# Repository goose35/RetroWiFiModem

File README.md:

# Retro WiFi modem

Forked from BenMtl's repository.
Modified to use a NodeMCU board, of which i had several in waiting.
Will be using on a C64, BBC Micro and Amiga A1200 so will require several adapter leads

# Important Note

Please note that there are 2 standards (pin-outs) for the 10 pin motherboard connector
AT/Everex or Intel/DTK
This modem is using the Intel/DTK pinout
Therefore be aware of this when buying/making your connections to the modem serial port

## The Software

In a nod to its popularity, the command set I used largely follows that
used in [Paul Rickards' WiFi232](http://biosrhythm.com/?page_id=1453)
modem. Even if the innards are completely different, it made sense to
make it *work* like what people were already used to. There's a reason
everyone's been copying the Hayes command set for almost 40 years!

### First time setup

The default serial configuration is 1200bps, 8 data bits, no parity, 1
stop bit.

Here's the commands you need to set up the modem to automatically
connect to your WiFi network:

1. `AT$SSID=your WiFi network name` to set the WiFi network that the
modem will connect to when it powers up.
2. `AT$PASS=your WiFi network password` to set the password for the
network.
3. `ATC1` to connect to the network.
4. Optional stuff:
   * `AT$SB=speed` to set the default serial speed.
   * `AT$SU=dps` to set the data bits, parity and stop bits.
   * `ATNETn` to select whether or not to use Telnet protocol.
   * `AT&Kn` to use RTS/CTS flow control or not.
5. `AT&W` to save the settings.

Once you've done that, the modem will automatically connect to your WiFi
network on power up and will be ready to "dial up" a connection with
ATDT.

### Command Reference

Multiple AT commands can be typed in on a single line. Spaces between
commands are allowed, but not within commands (i.e. AT S0=1 X1 Q0 is
fine; ATS 0=  1 is not). Commands that take a string as an argument
(e.g. AT$SSID=, AT$TTY=) assume that *everything* that follows is a part
of the string, so no commands are allowed after them.

Command | Details
------- | -------
+++     | Online escape code. Once your modem is connected to another device, the only command it recognises is an escape code of a one second pause followed by three typed plus signs and another one second pause, which puts the modem back into local command mode.
A/      | Repeats the last command entered. Do not type AT or press Enter.
AT      | The attention prefix that precedes all command except A/ and +++.
AT?     | Displays a help cheatsheet.
ATA     | Force the modem to answer an incoming connection when the conditions for auto answer have not been satisfied.
ATC?<br>ATC*n* | Query or change the current WiFi connection status. A result of 0 means that the modem is not connected to WiFi, 1 means the modem is connected. The command ATC0 disconnects the modem from a WiFi connection. ATC1 connects the modem to the WiFi.
ATDS*n* | Calls the host specified in speed dial slot *n* (0-9).
ATDT<i>[+=-]host[:port]</i> | Tries to establish a WiFi TCP connection to the specified host name or IP address. If no port number is given, 23 (Telnet) is assumed. You can also use ATDT to dial one of the speed dial slots in one of two ways:<br><br><ul><li>The alias in each speed dial slot is checked to see if it matches the specified hostname.</li><li>A host specified as 7 identical digits dials the slot indicated by the digit. (i.e. 2222222 would speed dial the host in slot 2).</li></ul>Preceding the host name or IP address with a +, = or - character overrides the ATNET setting for the period of the connection.<br><br><ul><li>**+** forces NET2 (fake Telnet)</li><li>**=** forces NET1 (real Telnet)</li><li>**-** forces NET0 (no Telnet)</li></ul>Once the dial attempt has begun, pressing any key before the connection is established will abort the attempt.
ATE?<br>ATE*n* | Command mode echo. Enables or disables the display of your typed commands.<br><br><ul><li>E0 Command mode echo OFF. Your typing will not appear on the screen.</li><li>E1 Command mode echo ON. Your typing will appear on the screen.</li></ul>
ATGET*http&#58;//host[/page]* | Displays the contents of a website page. **https** connections are not supported. Once the contents have been displayed, the connection will automatically terminate.
ATH | Hangs up (ends) the current connection.
ATI | Displays the current network status, including sketch build date, WiFi and call connection state, SSID name, IP address, and bytes transferred.
ATNET?<br>ATNET*n* | Query or change whether telnet protocol is enabled. A result of 0 means that telnet protocol is disabled; 1 is *Real* telnet protocol and 2 is *Fake* telnet protocol. If you are connecting to a telnet server, it may expect the modem to respond to various telnet commands, such as terminal name (set with `AT$TTY`), terminal window size (set with `AT$TTS`) or terminal speed. Telnet protocol should be enabled for these sites, or you will at best see occasional garbage characters on your screen, or at worst the connection may fail.<br><br>The difference between *real* and *fake* telnet protocol is this: with *real* telnet protocol, a carriage return (CR) character being sent from the modem to the telnet server always has a NUL character added after it. The implementation of the telnet protocol used by some BBSes doesn't properly strip out the NUL character. When connecting to such BBSes (Particles! is one), use *fake* telnet.<br><br>When using *real* telnet protocol, when the telnet server sends a CR character followed by a NUL character, only the CR character will be sent to the serial port; the NUL character will be silently stripped out. With *fake* telnet protocol, the NUL will be passed through.
ATO | Return online. Use with the escape code (+++) to toggle between command and online modes.
ATQ?<br>ATQ*n* | Enable or disable the display of result codes. The default is Q0.<br><br><ul><li>Q0 Display result codes.</li><li>Q1 Suppress result codes (quiet).</li></ul>
ATRD<br>ATRT | Displays the current UTC date and time from NIST in the format *YY-MM-DD HH:MM:SS*. A WiFi connection is required and you cannot be connected to another site.
ATS0?<br>ATS0=*n* | Display or set the number of "rings" before answering an incoming connection. Setting `S0=0` means "don't answer".
ATV?<br>ATV*n* | Display result codes in words or numbers. The default is V1.<br><br><ul><li>V0 Display result codes in numeric form.</li><li>V1 Display result codes in text form.</li></ul>
ATX?<br>ATX*n* | Control the amount of information displayed in the result codes. The default is X1 (extended codes).<br><br><ul><li>X0 Display basic codes (CONNECT, NO CARRIER)</li><li>X1 Display extended codes (CONNECT speed, NO CARRIER (connect time))</li></ul>
ATZ | Resets the modem.
AT&F | Reset the NVRAM contents and current settings to the sketch defaults. All settings, including SSID name, password and speed dial slots are affected.
AT&K?<br>AT&K*n* | Data flow control. Prevents the modem's buffers for received and transmitted from overflowing.<br><br><ul><li>&K0 Disable data flow control.</li><li>&K1 Use hardware flow control. Requires that your computer and software support Clear to Send (CTS) and Request to Send (RTS) at the RS-232 interface.</li></ul>
AT&R?<br>AT&R=*server pwd* | Query or change the password for incoming connections. If set, the user has 3 chances in 60 seconds to enter the correct password or the modem will end the connection.
AT&V*n* | Display current or stored settings.<br><br><ul><li>&V0 Display current settings.</li><li>&V1 Display stored settings.</li></ul>
AT&W | Save current settings to NVRAM.
AT&Zn?<br>AT&Z*n*=*host[:port],alias* | Store up to 10 numbers in NVRAM, where *n* is the position 0-9 in NVRAM, and *host[:port]* is the host string, and *alias* is the speed dial alias name. The host string may be up to 50 characters long, and the alias string may be up to 16 characters long.<br><br>Example: `AT&Z2=particlesbbs.dyndns.org:6400,particles`<br><br>This number can then be dialed in any of the following ways:<br><br><ul><li>`ATDS2`</li><li>`ATDTparticles`</li><li>`ATDT2222222`</li></ul>
AT$AE?<br>AT$AE=*startup AT cmd* | Query or change the command line to be executed when the modem starts up.
AT$BM?<br>AT$BM=*server busy msg* | Query or change a message to be returned to an incoming connection if the modem is busy (i.e. already has a connection established).
AT$MDNS<br>AT$MDNS=*mDNS name* | Query or change the mDNS network name (defaults to "espmodem"). When a non zero TCP port is defined, you can telnet to that port with **telnet mdnsname.local port**.
AT$PASS?<br>AT$PASS=*WiFi pwd* | Query or change the current WiFi password. The password is case sensitive. Clear the password by issuing the set command with no password. The maximum length of the password is 64 characters.
AT$SB?<br>AT$SB=*n* | Query or change the current baud rate. Valid values for "n" are 110, 300, 450, 600, 710, 1200, 2400, 4800, 9600, 19200, 38400, 57600, 76800 and 115200. Any other value will return an ERROR message. The default baud rate is 1200. The Retro WiFi modem does not automatically detect baud rate like a dial-up modem. The baud rate setting must match that of your terminal to operate properly. It will display garbage in your terminal otherwise.
AT$SP?<br>AT$SP=*n* | TCP server port to listen on. A value of 0 means that the TCP server is disabled, and no incoming connections are allowed.
AT$SSID?<br>AT$SSID=*ssid name* | Query or change the current SSID to the specified name. The given SSID name is case sensitive. Clear the SSID by issuing the set command with no SSID. The maximum length of the SSID name is 32 characters.
AT$SU?<br>AT$SU=*dps* | Query or change the current number of data bits ('d'), parity ('p') and stop bits ('s") of the serial UART. Valid values for 'd' are 5, 6, 7 or 8 bits. Valid values for 'p' are (N)one, (O)dd or (E)ven parity. Valid values for 's' are 1 or 2 bits. The default settings are 8N1. The UART setting must match your terminal to work properly.
AT$TTL?<br>AT$TTL=*telnet location* | Query or change the Telnet location value to be returned when the Telnet server issues a SEND-LOCATION request. The default value is "Computer Room".
AT$TTS?<br>AT$TTS=*WxH* | Query or change the window size (columns x rows) to be returned when the Telnet server issues a NAWS (Negotiate About Window Size) request. The default value is 80x24. For terminals that are smaller than 80x24, setting these values appropriately will enable paging on the help (AT?) and network status (ATI) commands.
AT$TTY?<br>AT$TTY=*terminal type* | Query or change the terminal type to be returned when the Telnet server issues a TERMINAL-TYPE request. The default value is "ansi".
AT$W?<br>AT$W=*n* | Startup wait.<br><br><ul><li>$W=0 Startup with no wait.</li><li>$W=1 Wait for the return key to be pressed at startup.</li></ul>

### Updating the Software

While I liked the idea of being able to update the software OTA, it
seemed to make more sense in my situation to be able to *push* a new
version as I built it rather than have the modem *pull* it. So that's
what I did. It uses the default OTA upload capability built into the
Arduino IDE.

**Jan 24/22:** It's been reported that the ESP8266 core is slightly
snafu'd at the moment, and that it's breaking things in the modem
software. As a workaround, I've added the bin file that gets uploaded
to the modem in the repository. I haven't updated my ESP8266 core in
ages; "if it isn't broken, don't break it", and everything still works
for me. The bin file can be uploaded with the *espota.py* tool in the
ESP8266 tool directory tree.

(If TPTB have deleted/renamed/moved that tool in the current core,
you'll have to figure out how to do a manual OTA update.)

### RTS/CTS handshaking and a dead spin loop issue

Something I noticed with ESP8266 software that puzzled me was the
number of places I saw a series of Serial print statements being broken
up with calls to yield(), like so:

```
   Serial.print("Hello world!\n");
   yield();
   Serial.print("How are you today?\n");
   yield();
```
It didn't take long to figure out what was going on; The print() call
was blocking, and at lower baud rates, even printing a few relatively
short strings was enough to cause the watchdog to bark and cause a
reset. So the repetitive yield() calls were an attempt to feed the
watchdog often enough to keep it from barking.

What does this have to do with RTS/CTS handshaking? Simply put,
lowering RTS for more than a few seconds was causing the watchdog to
bark as well. So I started digging.

In cores/esp8266/uart.cpp I found the following function:

```
static void
uart_do_write_char(const int uart_nr, char c)
{
    while(uart_tx_fifo_full(uart_nr));

    USF(uart_nr) = c;
}
```

This is the low level function that everything calls to send a character
out the serial port. The cause of the watchdog barking is in the dead
spin while loop. It waits until there's room in the transmit FIFO to add
another character. So if RTS/CTS handshaking is enabled, and RTS is low
for longer than the watchdog likes: woof.

What I did to quiet the watchdog down both when sending long strings at
low baud rates and during long waits for RTS to come active again was to
add a yield() call to the dead spin while loop, like so:

```
static void
uart_do_write_char(const int uart_nr, char c)
{
    while(uart_tx_fifo_full(uart_nr))
      yield();

    USF(uart_nr) = c;
}
```

This way, no matter how long the code has to wait for space in the
transmit FIFO, the watchdog is kept well fed and quiet.

## Status

Is a personal project like this ever *really* finished? I've had two
units assembled and in use since the spring of 2020, and while there's
been some software changes since then, I really don't expect any more.
There are no outstanding bugs that I'm aware of, and no new features on
my wish list. For the time being at least, I think it's complete.

### Linux, Telnet, Zmodem and downloading binary files

Have you used the modem to 'dial' into a Linux box? And have you done a
`sz binary_file` on the Linux box? And at a completely reproducible
point in the file, has the connection dropped? But other binary files
work just fine? Then read on.

This drove me slightly batty for months. I finally narrowed it down to
trying to send blocks of binary data with a large number of FF bytes. I
eventually created a test file consisting of 2K of FF and used that to
test with. I could download it through the modem with Xmodem just fine.
Ymodem also worked if I kept the block size down to 128 bytes - but the
connection would drop instantly if I tried sending 1K blocks. Same thing
with Zmodem.

In fact, if I just tried `cat binary_file`, the connection would
drop. Which eventually got me thinking. Sitting at the console on my
main Linux box, I telnet'd to the same box and logged in. No WiFi modem
involved anywhere, just a telnet session on the console to the same box.
I then did a `cat binary_file`. The telnet connection dropped, and I
was back in my original session.

It's the Linux telnet daemon. Not the modem at all.

To prove it to myself, I hooked up WiFi modems to two systems on their
serial ports and had one dial into the other. I could send the all FF
binary file back and forth with Zmodem and Ymodem, no trouble at all.

But you really, really need to download that binary file through the
modem from a telnet connection to a Linux box? You're not going to be
able to use Zmodem. Ymodem will work (the sy command defaults to 128
byte blocks), as will Xmodem. But not Zmodem.

Oddly enough, the telnet daemon has no trouble *receiving* the all FF
binary file. Only sending it. Your guess as to why is probably better
than mine.

## References

* [WiFi232 - An Internet Hayes Modem for your Retro Computer](http://biosrhythm.com/?page_id=1453)<br>
* [WiFi232's Evil Clone](https://forum.vcfed.org/index.php?threads/wifi232s-evil-clone.1070412/)<br>
* [Jussi Salin's Virtual modem for ESP8266](https://github.com/jsalin/esp8266_modem)<br>
* [Stardot's ESP8266 based virtual modem](https://github.com/stardot/esp8266_modem)<br>
* [Roland Juno's ESP8266 based virtual modem](https://github.com/RolandJuno/esp8266_modem)

## Acknowledgements

* A whole lot of people owe a big vote of thanks to Jussi Salin for
releasing their virtual modem code for the ESP8266 and starting the
ball rolling.
* Paul Rickards for an amazing bit of hardware to draw inspiration from.
* All the Stardot contributors for their work.
* And, of course, Dennis C. Hayes for creating something so simple and
elegant that has stood the test of time.

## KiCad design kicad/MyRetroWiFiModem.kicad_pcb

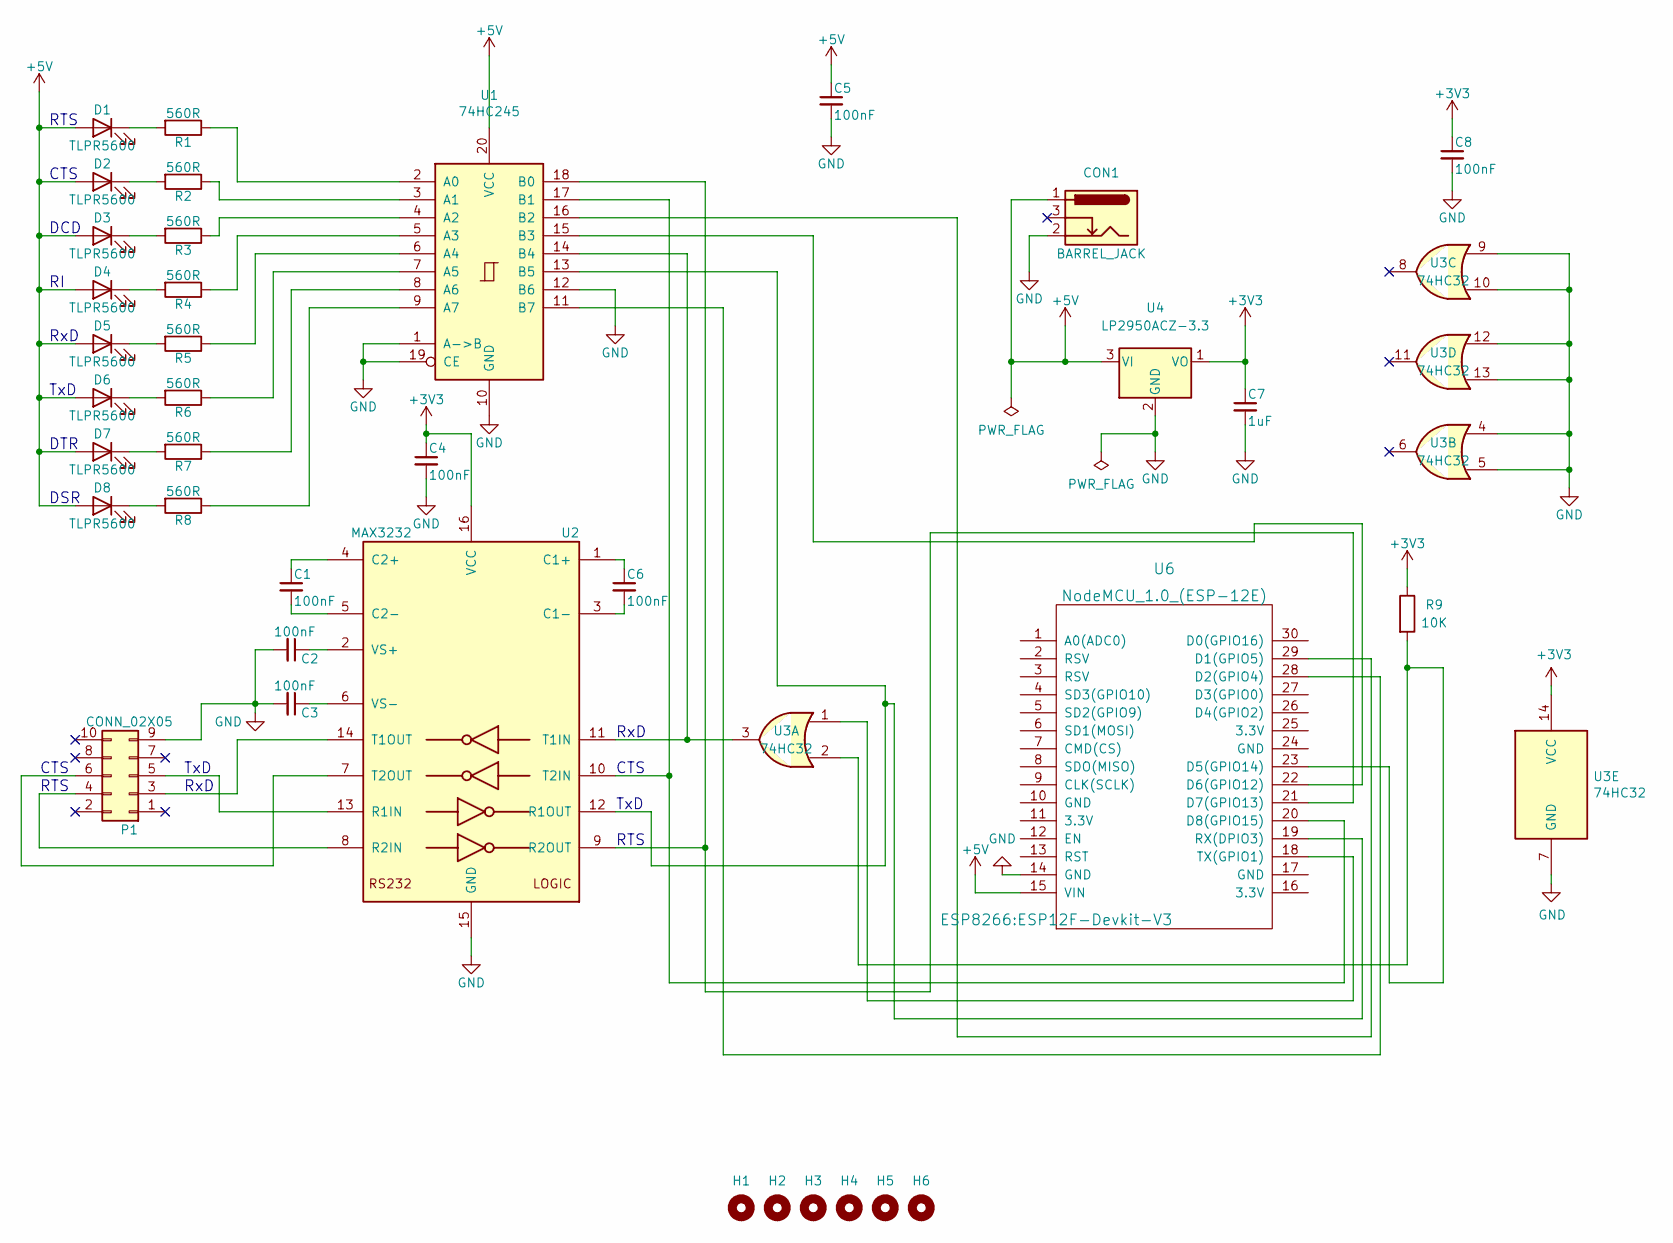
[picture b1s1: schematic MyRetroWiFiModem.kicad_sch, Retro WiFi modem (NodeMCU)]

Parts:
C1, C2, C3, C4, C5, C8: 100nF; C_Disc_D3.0mm_W2.0mm_P2.50mm; DigiKey PN 399-9859-1-ND
C6: 100nF; C_Disc_D5.0mm_W2.5mm_P2.50mm; DigiKey PN 399-9843-ND
C7: 1uF; C_Disc_D5.0mm_W2.5mm_P5.00mm; DigiKey PN 399-3529-ND
CON1: BARREL_JACK; BarrelJack_Horizontal; DigiKey PN 839-54-00166-ND
D1, D2, D3, D4, D5, D6, D7, D8: TLPR5600; LED_D3.0mm; DigiKey PN TLPR5600-ND
H1, H2, H3, H4, H5, H6: MountingHole; MountingHole_3.2mm_M3
P1: CONN_02X05; IDC-Header_2x05_P2.54mm_Vertical; DigiKey PN ED1543-ND
R1, R2, R3, R4, R5, R6, R7, R8: 560R; R_Axial_DIN0204_L3.6mm_D1.6mm_P7.62mm_Horizontal; DigiKey PN CF18JT560RCT-ND
R9: 10K; R_Axial_DIN0204_L3.6mm_D1.6mm_P7.62mm_Horizontal; DigiKey PN CF18JT10K0CT-ND
U1: 74HC245; DIP-20_W7.62mm; DigiKey PN 296-1612-5-ND
U2: MAX3232; DIP-16_W7.62mm; DigiKey PN ICL3232CPZ-ND
U3: 74HC32; DIP-14_W7.62mm; DigiKey PN 296-1589-5-ND
U4: LP2950ACZ-3.3; TO-92L_Inline_Wide; DigiKey PN LP2950ACZ-3.3GOS-ND
U6: NodeMCU_1.0_(ESP-12E); ESP12F-Devkit-V3

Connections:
+3V3: C4.1, C7.1, C8.1, R9.1, U2.16 (VCC), U3.14 (VCC), U4.1 (VO)
+5V: C5.1, CON1.1, D1.2 (A), D2.2 (A), D3.2 (A), D4.2 (A), D5.2 (A), D6.2 (A), D7.2 (A), D8.2 (A), U1.20 (VCC), U4.3 (VI), U6.15 (VIN)
GND: C2.2, C3.2, C4.2, C5.2, C7.2, C8.2, CON1.2, P1.9, U1.1 (A->B), U1.10 (GND), U1.12 (B6), U1.19 (CE), U2.15 (GND), U3.4, U3.5, U3.7 (GND), U3.9, U3.10, U3.12, U3.13, U4.2 (GND), U6.14 (GND)
unnamed: C1.1, U2.4 (C2+)
unnamed: C1.2, U2.5 (C2-)
unnamed: C2.1, U2.2 (VS+)
unnamed: C3.1, U2.6 (VS-)
unnamed: C6.1, U2.1 (C1+)
unnamed: C6.2, U2.3 (C1-)
unnamed: D1.1 (K), R1.2
unnamed: D2.1 (K), R2.2
unnamed: D3.1 (K), R3.2
unnamed: D4.1 (K), R4.2
unnamed: D5.1 (K), R5.2
unnamed: D6.1 (K), R6.2
unnamed: D7.1 (K), R7.2
unnamed: D8.1 (K), R8.2
unnamed: P1.3, U2.14 (T1OUT)
unnamed: P1.4, U2.8 (R2IN)
unnamed: P1.5, U2.13 (R1IN)
unnamed: P1.6, U2.7 (T2OUT)
unnamed: R1.1, U1.2 (A0)
unnamed: R2.1, U1.3 (A1)
unnamed: R3.1, U1.4 (A2)
unnamed: R4.1, U1.5 (A3)
unnamed: R5.1, U1.6 (A4)
unnamed: R6.1, U1.7 (A5)
unnamed: R7.1, U1.8 (A6)
unnamed: R8.1, U1.9 (A7)
unnamed: R9.2, U3.2, U6.23 (D5(GPIO14))
unnamed: U1.11 (B7), U6.28 (D2(GPIO4))
unnamed: U1.13 (B5), U2.12 (R1OUT), U6.19 (RX(DPIO3))
unnamed: U1.14 (B4), U2.11 (T1IN), U3.3
unnamed: U1.15 (B3), U6.22 (D6(GPIO12))
unnamed: U1.16 (B2), U6.29 (D1(GPIO5))
unnamed: U1.17 (B1), U2.10 (T2IN), U6.20 (D8(GPIO15))
unnamed: U1.18 (B0), U2.9 (R2OUT), U6.21 (D7(GPIO13))
unnamed: U3.1, U6.18 (TX(GPIO1))

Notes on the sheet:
TxD
CTS
RxD
RTS
DSR
DCD
DTR

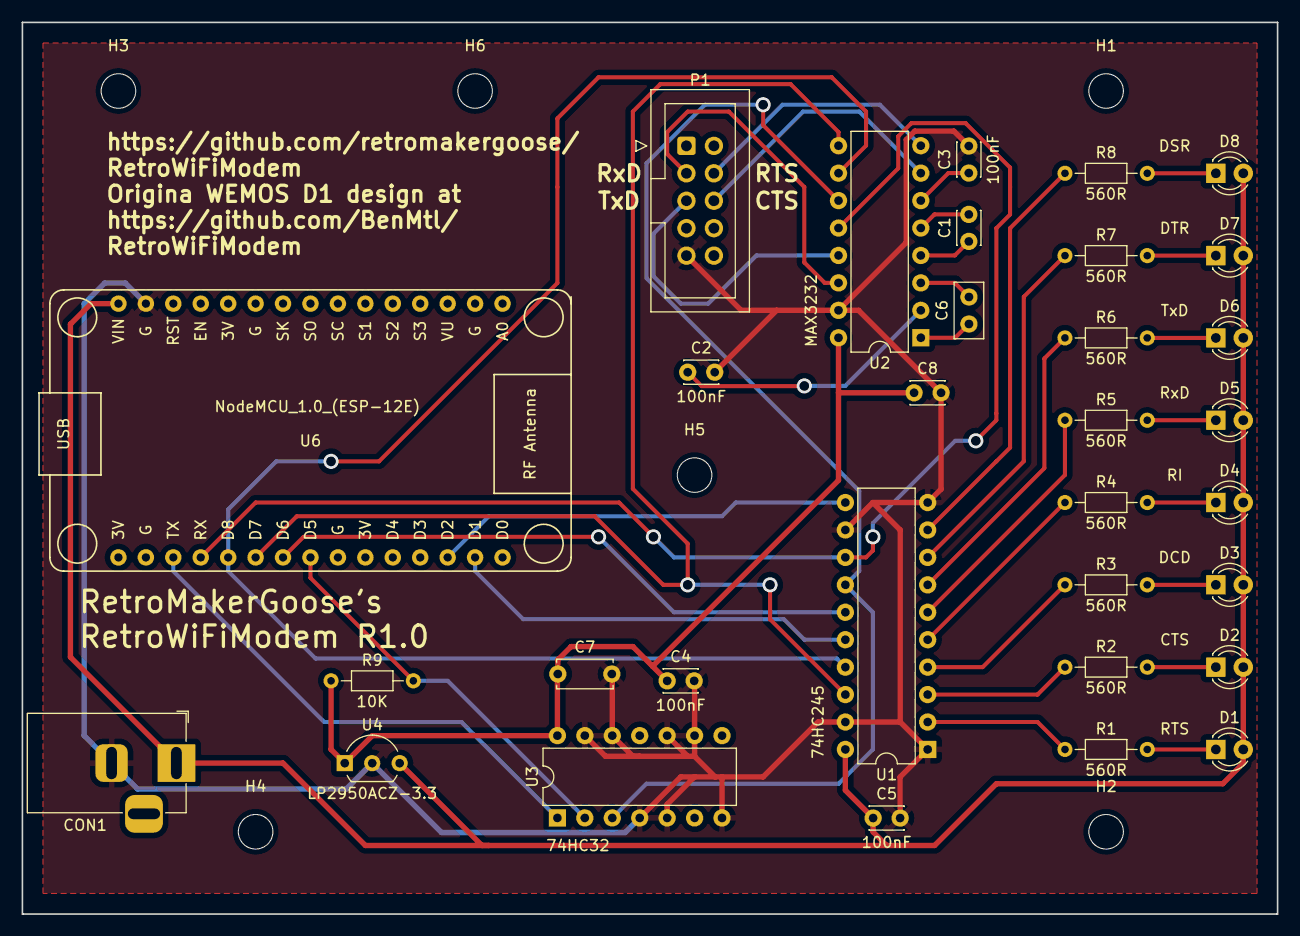
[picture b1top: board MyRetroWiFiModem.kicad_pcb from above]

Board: 2 copper layers, 116.2 x 82.5 mm, 38 parts (0 on the bottom side), 38 nets.

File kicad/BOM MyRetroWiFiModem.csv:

"Id";"Designator";"Package";"Quantity";"Designation";"Supplier and ref";
1;"U6";"NodeMCU1.0(12-E)";1;"NodeMCU_1.0_(ESP-12E)";;;
2;"C2,C3,C4,C8,C5,C1";"C_Disc_D3.0mm_W2.0mm_P2.50mm";6;"100nF";;;
3;"R9";"R_Axial_DIN0204_L3.6mm_D1.6mm_P7.62mm_Horizontal";1;"10K";;;
4;"R7,R5,R6,R4,R8,R3,R1,R2";"R_Axial_DIN0204_L3.6mm_D1.6mm_P7.62mm_Horizontal";8;"560R";;;
5;"H4,H3,H1,H6,H2,H5";"MountingHole_3.2mm_M3";6;"MountingHole";;;
6;"U1";"DIP-20_W7.62mm";1;"74HC245";;;
7;"P1";"IDC-Header_2x05_P2.54mm_Vertical";1;"CONN_02X05";;;
8;"D5,D8,D4,D2,D7,D1,D6,D3";"LED_D3.0mm";8;"TLPR5600";;;
9;"C6";"C_Disc_D5.0mm_W2.5mm_P5.00mm";1;"100nF";;;
10;"U4";"TO-92L_Inline_Wide";1;"LP2950ACZ-3.3";;;
11;"CON1";"BarrelJack_Horizontal";1;"BARREL_JACK";;;
12;"U2";"DIP-16_W7.62mm";1;"MAX3232";;;
13;"U3";"DIP-14_W7.62mm";1;"74HC32";;;
14;"C7";"C_Disc_D3.0mm_W2.0mm_P2.50mm";1;"1uF";;;

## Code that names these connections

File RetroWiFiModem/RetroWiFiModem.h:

#ifndef _MODEM_H
   #define _MODEM_H

   #define DEBUG                 0
   #define DEFAULT_SPEED         1200

   #define RING_INTERVAL         1500
   #define MAX_CMD_LEN           256
   #define TX_BUF_SIZE           256
   #define ESC_CHAR              '+'
   #define ESC_COUNT             3
   #define GUARD_TIME            1000
   #define MAGIC_NUMBER          0x4321
   #define MAX_SSID_LEN          32
   #define MAX_WIFI_PWD_LEN      64
   #define DEFAULT_LISTEN_PORT   6400
   #define TELNET_PORT           23
   #define HTTP_PORT             80
   #define SPEED_DIAL_SLOTS      10
   #define MAGIC_ANSWER_RINGS    3
   #define MAX_ALIAS_LEN         16
   #define MAX_SPEED_DIAL_LEN    50
   #define MAGIC_SPEED_LEN       7
   #define MAX_MDNSNAME_LEN      80
   #define MAX_BUSYMSG_LEN       80
   #define MAX_PWD_LEN           80
   #define PASSWORD_TIME         60000
   #define PASSWORD_TRIES        3
   #define MAX_AUTOEXEC_LEN      80
   #define MAX_TERMINAL_LEN      80
   #define MAX_LOCATION_LEN      80

   #define NUL  '\x00'
   #define CTLC '\x03'
   #define BS   '\x08'
   #define LF   '\x0A'
   #define CR   '\x0D'
   #define DEL  '\x7F'

   #define NO_TELNET   ((uint8_t)0)
   #define REAL_TELNET ((uint8_t)1)
   #define FAKE_TELNET ((uint8_t)2)

   // Telnet codes
   #define VLSUP     ((uint8_t)0)
   #define VLREQ     ((uint8_t)1)
   #define LOC       ((uint8_t)23)
   #define TTYPE     ((uint8_t)24)
   #define NAWS      ((uint8_t)31)
   #define TSPEED    ((uint8_t)32)
   #define LFLOW     ((uint8_t)33)
   #define LINEMODE  ((uint8_t)34)
   #define XDISPLOC  ((uint8_t)35)
   #define NEW_ENVIRON ((uint8_t)39)
   #define BINARY    ((uint8_t)0)
   #define ECHO      ((uint8_t)1)
   #define SUP_GA    ((uint8_t)3)
   #define SE        ((uint8_t)240)
   #define SB        ((uint8_t)250)
   #define WILL      ((uint8_t)251)
   #define WONT      ((uint8_t)252)
   #define DO        ((uint8_t)253)
   #define DONT      ((uint8_t)254)
   #define IAC       ((uint8_t)255)

   #define NIST_HOST "time.nist.gov"
   #define NIST_PORT 13

   #define ACTIVE LOW           // RS232 control signals are active low

   // As the ESP8266 is being used as a modem (DCE) in this application,
    // I've reversed the naming of RTS/CTS to match what they'd be on
    // a modem. The usual naming is correct if the ESP8266 is wired up as
    // a DTE, but kept confusing me here as it's wired up as a DCE.
   #ifdef ARDUINO_ESP8266_WEMOS_D1R1
      // D1 R1 pins
      #define CTS D10           // (GPIO15) output
      #define RTS D11           // (GPIO13) input
      #define RI  D12           // (GPIO12) output
      #define DSR D4            // (GPIO04) output
      #define DCD D3            // (GPIO05) output
      #define TXEN D5           // (GPIO14) output
   #endif

   #ifdef ARDUINO_ESP8266_WEMOS_D1MINI
      // D1 mini pins
      #define CTS D8            // (GPIO15) output
      #define RTS D7            // (GPIO13) input
      #define RI  D6            // (GPIO12) output
      #define DSR D2            // (GPIO04) output
      #define DCD D1            // (GPIO05) output
      #define TXEN D5           // (GPIO14) output
   #endif

// added for NodeMCU 0.9 support
   #ifdef ARDUINO_ESP8266_NODEMCU_ESP12
      // D1 mini pins
      #define CTS D8            // (GPIO15) output
      #define RTS D7            // (GPIO13) input
      #define RI  D6            // (GPIO12) output
      #define DSR D2            // (GPIO04) output
      #define DCD D1            // (GPIO05) output
      #define TXEN D5           // (GPIO14) output
   #endif

// added for NodeMCU 1.0 support
    #ifdef ARDUINO_ESP8266_NODEMCU_ESP12E
      // D1 mini pins
      #define CTS D8            // (GPIO15) output
      #define RTS D7            // (GPIO13) input
      #define RI  D6            // (GPIO12) output
      #define DSR D2            // (GPIO04) output
      #define DCD D1            // (GPIO05) output
      #define TXEN D5           // (GPIO14) output
   #endif



#endif

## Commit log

2023-07-17 BBC serial cables
    One modem cable including the header cable for the Retro WiFi Modem
    A null modem (Crossover) cable for linking PC and BBC for file transfer
